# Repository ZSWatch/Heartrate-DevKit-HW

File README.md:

# ZSWatch-Heartrate-DevKit

## 📑 Table of Contents

- [ZSWatch-Heartrate-DevKit](#zswatch-heartrate-devkit)
  - [📑 Table of Contents](#-table-of-contents)
  - [📖 About](#-about)
  - [📂 Directory Breakdown](#-directory-breakdown)
  - [Purchasing](#purchasing)
  - [Ressources](#ressources)
  - [👨‍💻 Maintainer](#-maintainer)

## 📖 About

The **ZSWatch-Heartrate-DevKit** project provides the hardware design and production files for a heartrate development board tailored to the ZSWatch ecosystem.
It is built with **KiCad** and integrates a full **CI/CD pipeline** using **KiBot**, ensuring reproducible outputs for documentation, manufacturing, and releases.

Key features:

- 🛠️ Open-source hardware design
- 📦 Automated generation of Gerber, BoM, and documentation via KiBot
- 🔄 Workflow stages (DRAFT → PRELIMINARY → CHECKED → RELEASED) for structured releases
- 📝 Clear documentation and changelog to track progress
- 🌍 Designed with collaboration and transparency in mind

Please check the [wiki](https://github.com/ZSWatch/ZSWatch/wiki) for more information about the project.

You can also view this project on [CADLAB.io](https://cadlab.io/project/29659).

## 📂 Directory Breakdown

- **`.github`**: GitHub related files
- **`.gitignore`**: Ignored files list
- **`devkit`**: KiCad project for the devkit
- **`production`**: Manufacturing outputs (Gerbers, documentation, etc.)
- **`CHANGELOG.md`**: Version history
- **`LICENSE`**: Project license (GPL-3.0)
- **`README.md`**: Project overview

## Purchasing

TBD

## Ressources

- [KiBot Template](https://github.com/nguyen-v/KDT_Hierarchical_KiBot)

## 👨‍💻 Maintainer

- [Daniel Kampert](mailto:danielkameprt@kampis-elektroecke.de)

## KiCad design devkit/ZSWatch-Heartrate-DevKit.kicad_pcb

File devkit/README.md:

<h1 align="center">Template</h1>

<p align="center" width="100%">
  
</p>

***

<p align="center">
  
&nbsp; &nbsp; &nbsp; &nbsp;
  
</p>

***

## SPECIFICATIONS

| Parameter | Value |
| --- | --- |
| Dimensions | 32.0 × 24.0 mm |

***

## DIRECTORY STRUCTURE

    .
    ├─ Computations       # Misc calculations
    ├─ HTML               # HTML files for generated webpage
    ├─ Images             # Pictures and renders
    │
    ├─ kibot_resources    # External resources for KiBot
    │  ├─ colors          # Color theme for KiCad
    │  ├─ fonts           # Fonts used in the project
    │  ├─ scripts         # External scripts used with KiBot
    │  └─ templates       # Templates for KiBot generated reports
    │
    ├─ kibot_yaml         # KiBot YAML config files
    ├─ KiRI               # KiRI (PCB diff viewer) files
    │
    ├─ lib                # KiCad footprint and symbol libraries
    │  ├─ 3d_models       # Component 3D models
    │  ├─ lib_fp          # Footprint libraries
    │  └─ lib_sym         # Symbol libraries
    │
    ├─ Logos              # Logos
    │
    ├─ Manufacturing      # Assembly and fabrication documents
    │  ├─ Assembly        # Assembly documents (BoM, pos, notes)
    │  │
    │  └─ Fabrication     # Fabrication documents (ZIP, notes)
    │     ├─ Drill Tables # CSV drill tables
    │     └─ Gerbers      # Gerbers
    │
    ├─ Report             # Reports for ERC/DRC
    ├─ Schematic          # PDF of schematic
    ├─ Templates          # Title block templates
    ├─ Testing
    │  └─ Testpoints      # Testpoints tables      
    │
    └─ Variants           # Outputs for assembly variants

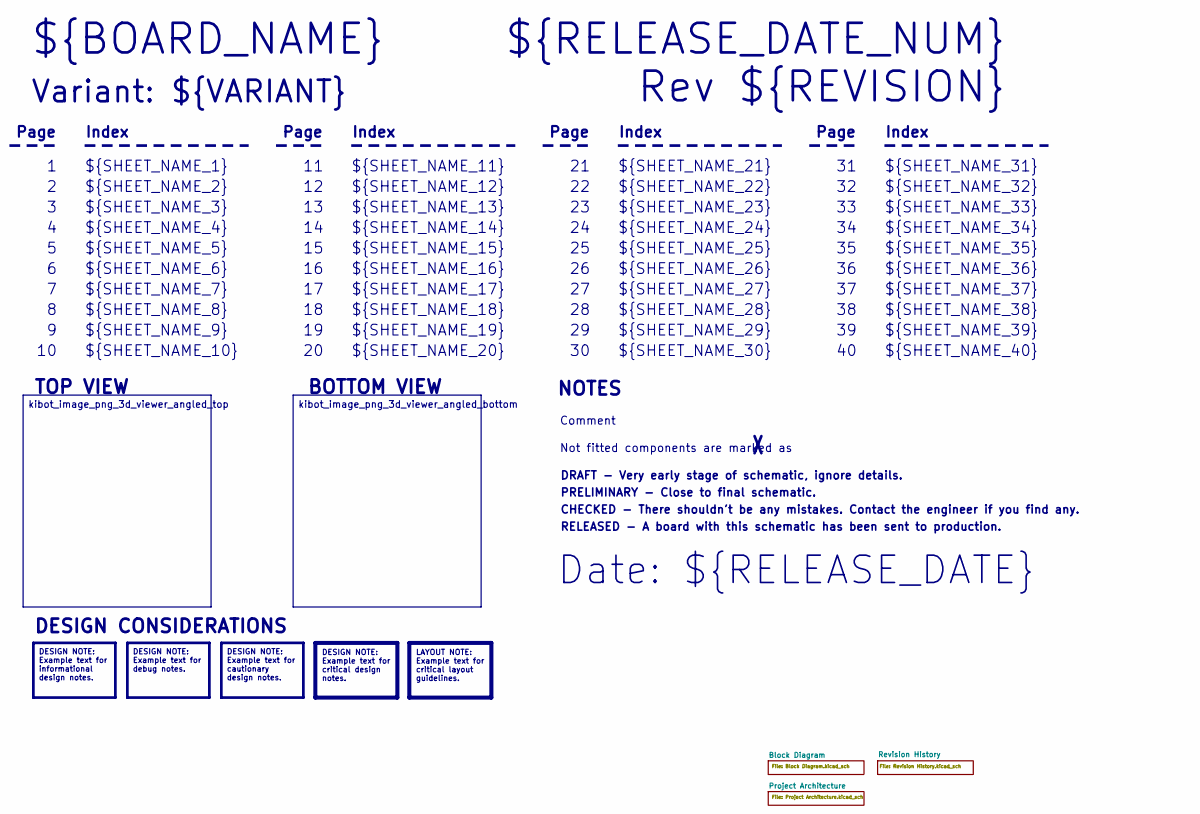
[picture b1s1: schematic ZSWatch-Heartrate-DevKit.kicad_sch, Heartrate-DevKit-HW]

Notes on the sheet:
Variant: ${VARIANT}
RELEASED - A board with this schematic has been sent to production.
${SHEET_NAME_24}
Index
Page
PRELIMINARY - Close to final schematic.
${SHEET_NAME_22}
DRAFT - Very early stage of schematic, ignore details.
${SHEET_NAME_12}
${SHEET_NAME_8}
${SHEET_NAME_2}
${SHEET_NAME_5}
${SHEET_NAME_20}
${SHEET_NAME_23}
${RELEASE_DATE_NUM}
${SHEET_NAME_35}
Not fitted components are marked as
${SHEET_NAME_11}
${SHEET_NAME_6}
${SHEET_NAME_37}
${SHEET_NAME_26}
${SHEET_NAME_36}
Rev ${REVISION}
${SHEET_NAME_15}
CHECKED - There shouldn't be any mistakes. Contact the engineer if you find any.
BOTTOM VIEW
${SHEET_NAME_14}
${SHEET_NAME_21}
${SHEET_NAME_17}
${SHEET_NAME_18}
Date: ${RELEASE_DATE}
${SHEET_NAME_7}
${SHEET_NAME_31}
${BOARD_NAME}
NOTES
${SHEET_NAME_40}
${SHEET_NAME_39}
${SHEET_NAME_32}
${SHEET_NAME_1}
${SHEET_NAME_9}

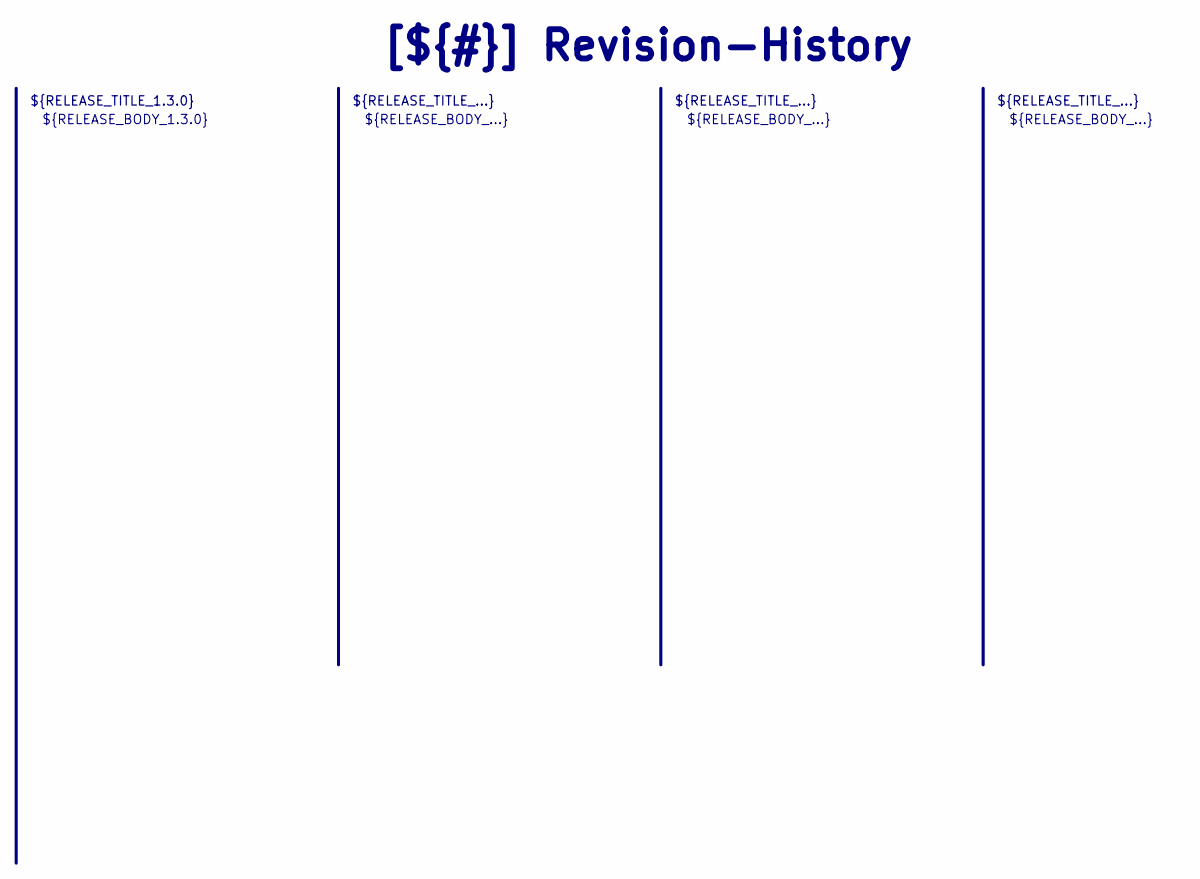
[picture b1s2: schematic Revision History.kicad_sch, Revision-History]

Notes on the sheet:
${RELEASE_BODY_...}
[${#}] ${TITLE}
${RELEASE_BODY_1.3.0}
${RELEASE_TITLE_...}
${RELEASE_TITLE_1.3.0}

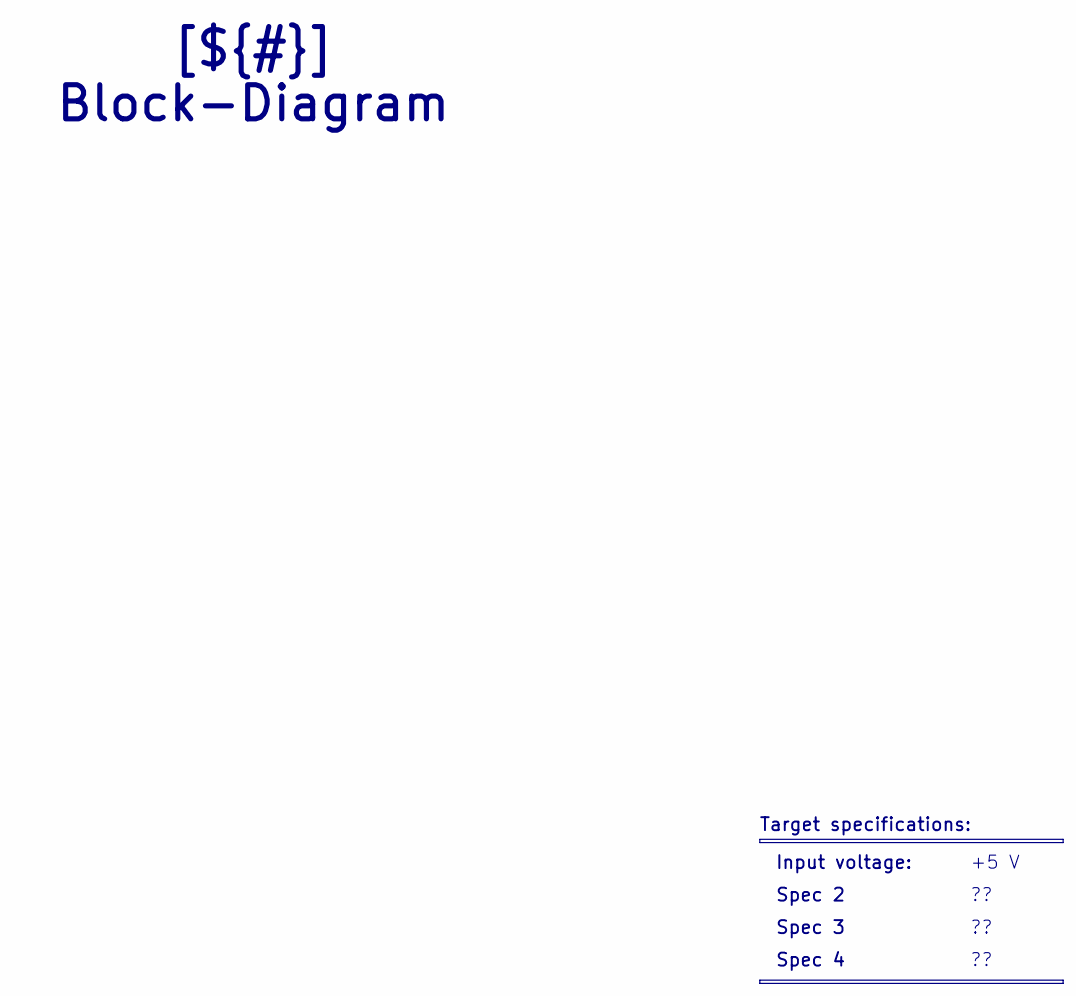
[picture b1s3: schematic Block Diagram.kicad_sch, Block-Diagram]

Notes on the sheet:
Spec 4
+5 V
[${#}] ${TITLE}
Input voltage:
Target specifications:
Spec 3
Spec 2

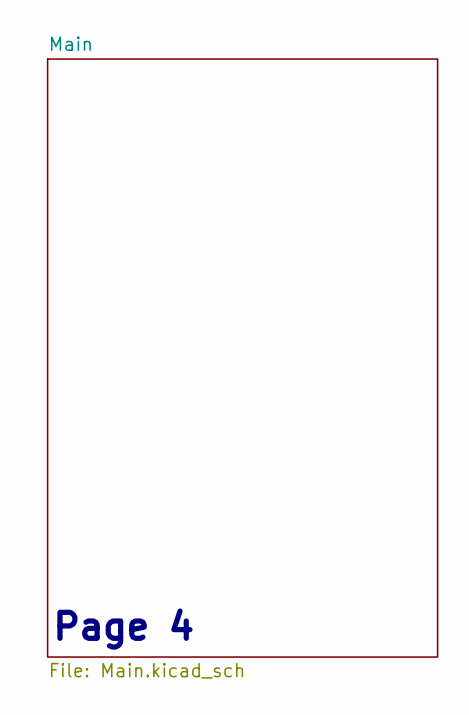
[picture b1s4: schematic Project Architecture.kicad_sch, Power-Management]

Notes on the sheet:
Page 4

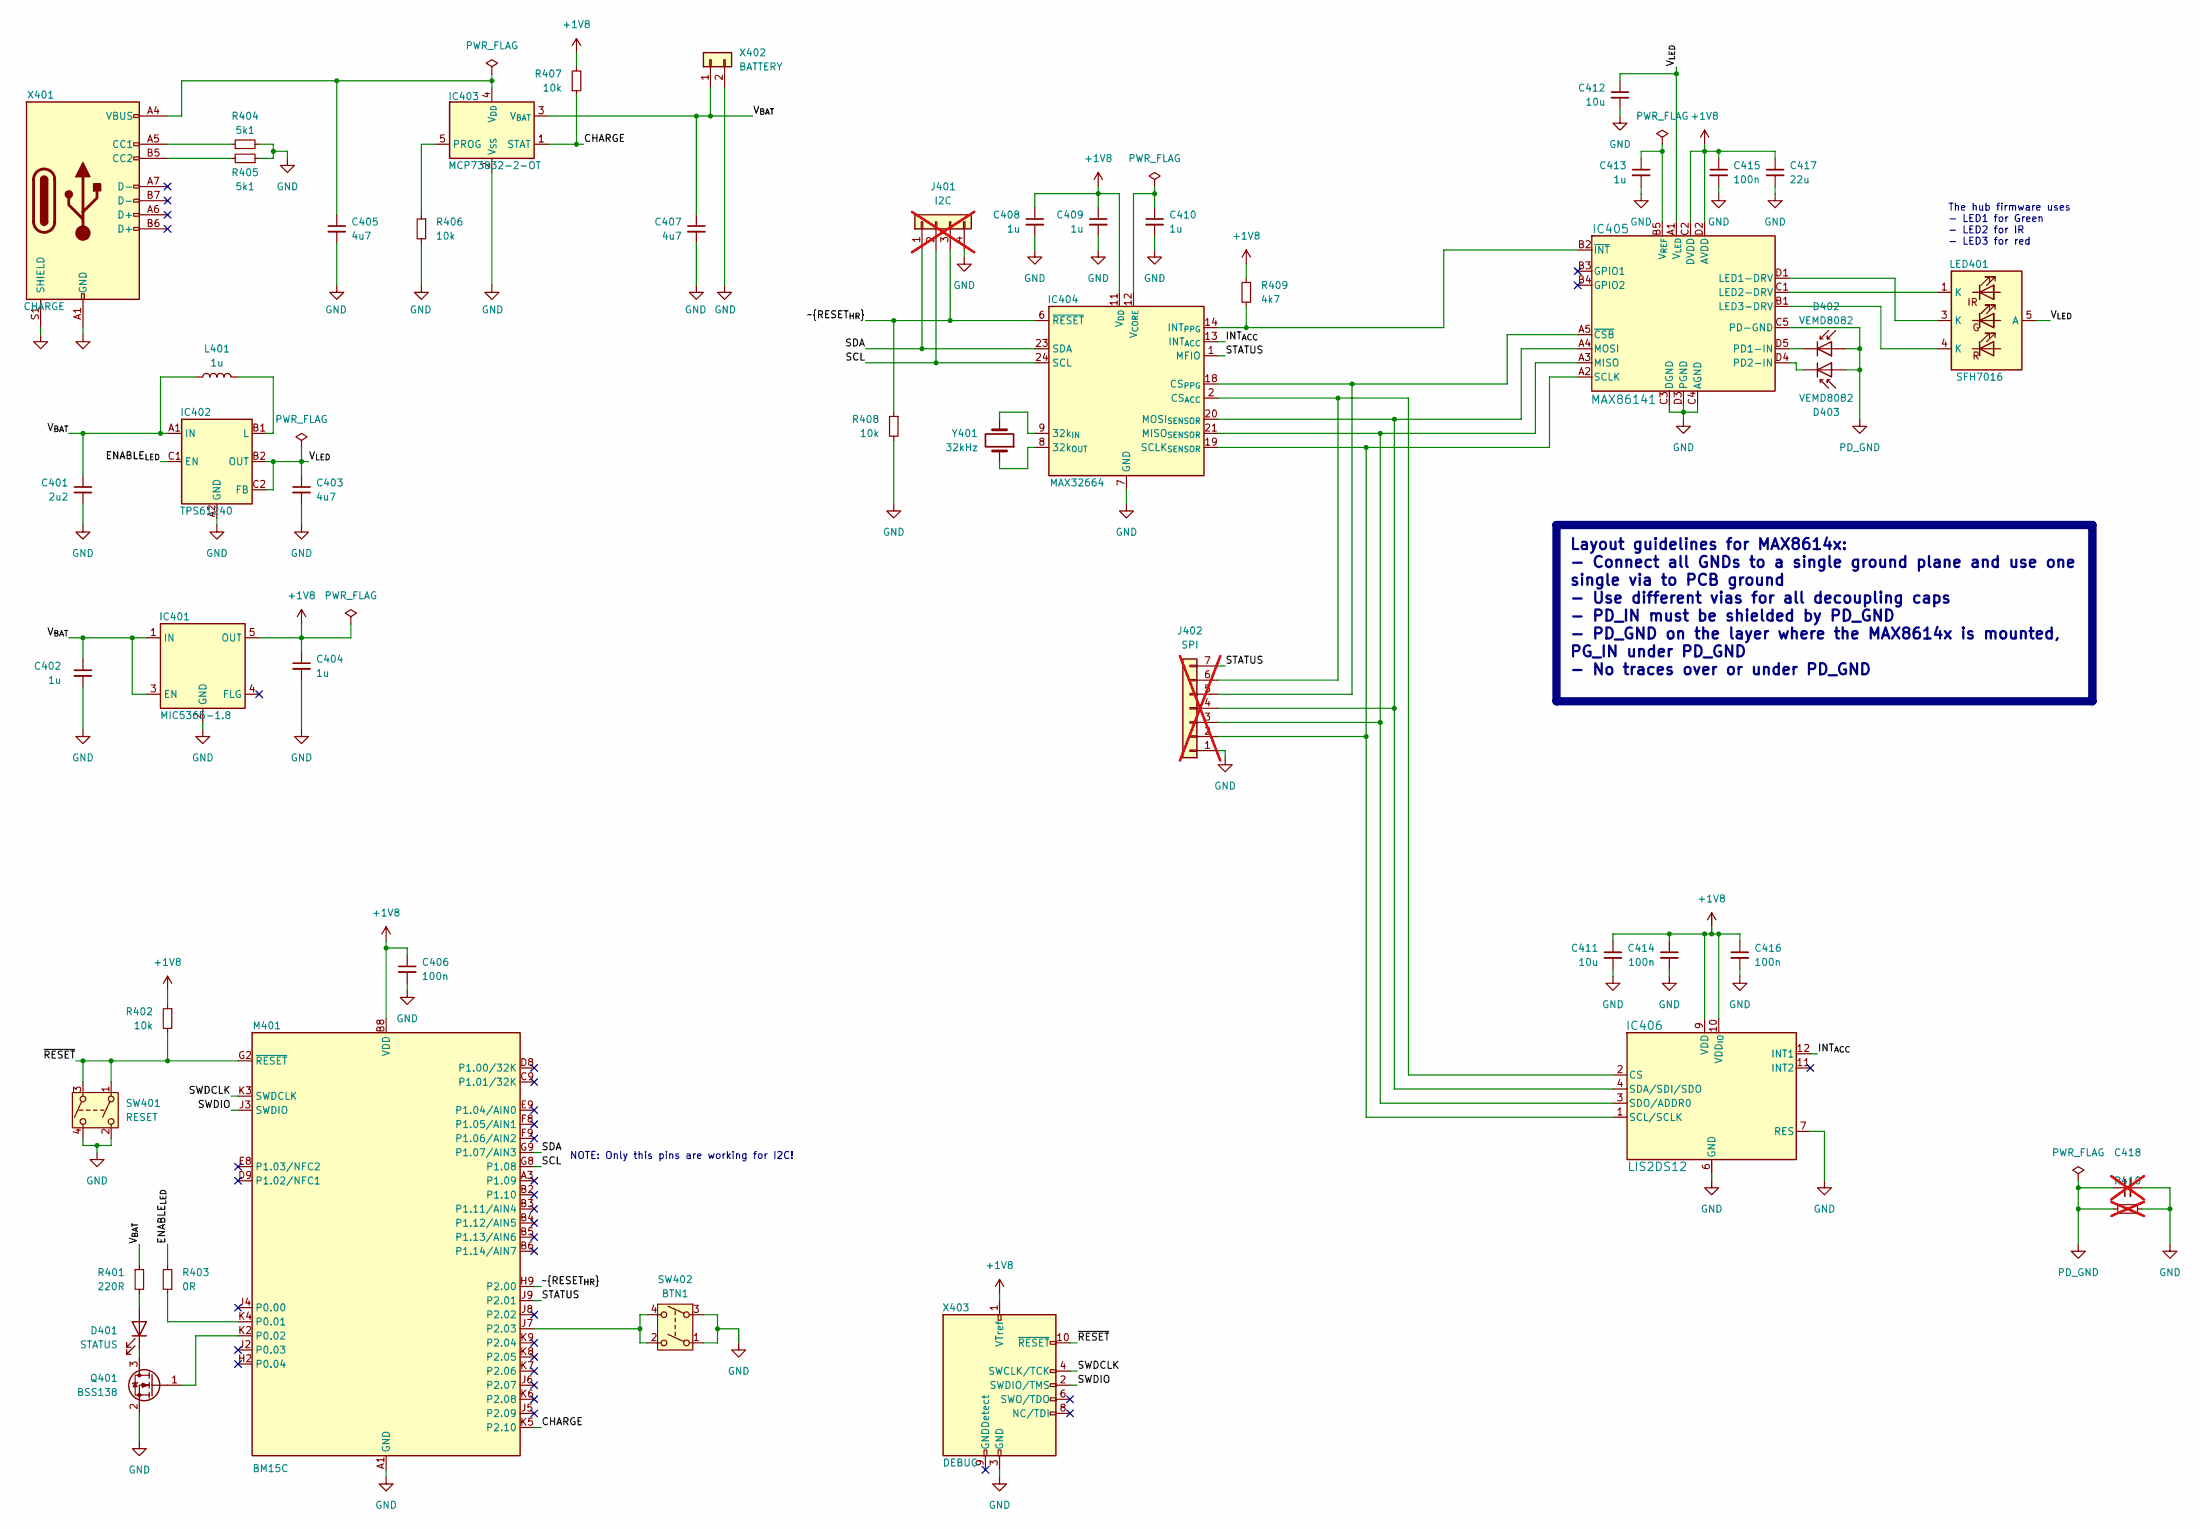
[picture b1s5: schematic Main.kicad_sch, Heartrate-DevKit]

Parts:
C401: 2u2; C_0603_1608Metric; mouser# 581-06033D225MAT2A
C402, C404: 1u; C_0603_1608Metric; mouser# 581-06035C105MAT2A
C403, C405, C407: 4u7; C_0603_1608Metric; mouser# 963-LMK107BJ475KA-T
C406, C414, C415, C416: 100n; C_0402_1005Metric; mouser# 80-C0402C104K4R7411
C408, C409, C410, C413: 1u; C_0402_1005Metric; mouser# 581-04023D105KAT2A
C411, C412: 10u; C_0402_1005Metric; mouser# 963-AMK105CBJ106MV-F
C417: 22u; C_0402_1005Metric; mouser# 963-MEASP105CC62261A
C418: C_0402_1005Metric; not fitted
D401: STATUS; LED_0805_2012Metric_Pad1.15x1.40mm_HandSolder; mouser# 630-HSMQ-C170-T0000
D402, D403: VEMD8082; VEMD808x; mouser# 78-VEMD8082
IC401: MIC5365-1.8; SOT-23-5; mouser# 998- MIC5365-1.8YD5-TR
IC402: TPS61240; DSBGA-6_0.886x1.288mm_2x3_P0.4mm; mouser# 595-TPS61240YFFR
IC403: MCP73832-2-OT; SOT-23-5; mouser# 579-MCP73832T-2ACI/OT
IC404: MAX32664; MAX32664GTG; mouser# 700-MAX32664GTGC+
IC405: MAX86141; THIN-WLP-20_2.228x1.967mm_P0.4mm; mouser# 700-MAX86141ENP+T
IC406: LIS2DS12; LGA-12_2x2mm_P0.5mm; mouser# 511-LIS2DS12
J401: I2C; PinHeader_1x04_P2.54mm_Vertical; not fitted
J402: SPI; PinHeader_1x07_P2.54mm_Vertical; not fitted
L401: 1u; L_0603_1608Metric; mouser# 815-ASMCI-0603-1R0MT
LED401: SFH7016; mouser# 720-SFH7016
M401: BM15C; mouser# 308-BM15C
Q401: BSS138; SOT-23; mouser# 512-BSS138
R401: 220R; R_0402_1005Metric; mouser# 652-CR0402-JW-221GLF
R402, R406, R407, R408: 10k; R_0402_1005Metric; mouser# 652-CR0402-JW-103GLF
R403: 0R; R_0805_2012Metric; mouser# 71-CRCW08050000Z0EBC
R404, R405: 5k1; R_0402_1005Metric; mouser# 652-CR0402-FX-5101GLF
R409: 4k7; R_0402_1005Metric; mouser# 603-RC0402FR-7D4K7L
R410: R_0402_1005Metric; not fitted
SW401: RESET; WS-TASV-6x6; mouser# 710-430182095816
SW402: BTN1; WS-TASV-6x6; mouser# 710-430182095816
X401: CHARGE; USB_C_Receptacle_GCT_USB4105-xx-A_16P_TopMnt_Horizontal; mouser# 640-USB4105-GF-A-120
X402: BATTERY; 78171-0002; mouser# 538-78171-0002
X403: DEBUG; PinHeader_2x05_P1.27mm_Vertical; mouser# 710-62201021121
Y401: 32kHz; ECS_ECX-1210; mouser# 520-.327-6-1210-TR

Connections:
+1V8: C404.1, C406.1, C408.1, C409.1, C411.1, C414.1, C415.1, C416.1, C417.1, IC401.5 (OUT), IC404.11 (V_{DD}), IC404.22 (V_{DD}), IC405.C2 (DVDD), IC405.D2 (AVDD), IC406.9 (VDD), IC406.10 (VDD_{IO}), M401.B8 (VDD), M401.C8 (VDD), R402.1, R407.2, R409.1, X403.1 (VTref)
/Project Architecture/Main/CHARGE: IC403.1 (STAT), M401.K5 (P2.10), R407.1
/Project Architecture/Main/ENABLE_{LED}: IC402.C1 (EN), R403.2
/Project Architecture/Main/INT_{ACC}: IC404.13 (INT_{ACC}), IC406.12 (INT1)
/Project Architecture/Main/SCL: IC404.24 (SCL), J401.2, M401.G8 (P1.08)
/Project Architecture/Main/SDA: IC404.23 (SDA), J401.1, M401.G9 (P1.07/AIN3)
/Project Architecture/Main/STATUS: IC404.1 (MFIO), J402.7, M401.J9 (P2.01)
/Project Architecture/Main/SWDCLK: M401.K3 (SWDCLK), X403.4 (SWCLK/TCK)
/Project Architecture/Main/SWDIO: M401.J3 (SWDIO), X403.2 (SWDIO/TMS)
/Project Architecture/Main/V_{BAT}: C401.1, C402.1, C407.1, IC401.1 (IN), IC401.3 (EN), IC402.A1 (IN), IC403.3 (V_{BAT}), L401.1, R401.1, X402.1
/Project Architecture/Main/V_{LED}: C403.1, C412.1, IC402.B2 (OUT), IC402.C2 (FB), IC405.A1 (V_{LED}), LED401.2 (A), LED401.5 (A)
/Project Architecture/Main/~RESET_{HR}: IC404.6 (~RESET), J401.3, M401.H9 (P2.00), R408.1
/Project Architecture/Main/~RESET: M401.G2 (~RESET), R402.2, SW401.1, SW401.3, X403.10 (~RESET)
GND: C401.2, C402.2, C403.2, C404.2, C405.2, C406.2, C407.2, C408.2, C409.2, C410.2, C411.2, C412.2, C413.2, C414.2, C415.2, C416.2, C417.2, C418.2, IC401.2 (GND), IC402.A2 (GND), IC403.2 (V_{SS}), IC404.7 (GND), IC404.10 (GND), IC405.C3 (DGND), IC405.C4 (AGND), IC405.D3 (PGND), IC406.6 (GND), IC406.7 (RES), IC406.8 (GND), J401.4, J402.1, M401.A1 (GND), M401.A9 (GND), M401.B1 (GND), M401.B7 (GND), M401.B9 (GND), M401.D1 (GND), M401.E1 (GND), M401.F1 (GND), M401.H8 (GND), Q401.2 (S), R404.2, R405.1, R406.2, R408.2, R410.2, SW401.2, SW401.4, SW402.1, SW402.3, X401.A1 (GND), X401.A12 (GND), X401.B1 (GND), X401.B12 (GND), X401.S1 (SHIELD), X402.2, X403.3 (GND), X403.5 (GND)
unnamed: D401.2 (A), R401.2
unnamed: D401.1 (K), Q401.3 (D)
unnamed: D402.1 (K), IC405.D5 (PD1-IN)
unnamed: D403.1 (K), IC405.D4 (PD2-IN)
unnamed: IC402.B1 (L), L401.2
unnamed: IC403.5 (PROG), R406.1
unnamed: C405.1, IC403.4 (V_{DD}), X401.A4 (VBUS), X401.A9 (VBUS), X401.B4 (VBUS), X401.B9 (VBUS)
unnamed: IC404.9 (32k_{IN}), Y401.2
unnamed: IC404.8 (32k_{OUT}), Y401.1
unnamed: IC404.2 (CS_{ACC}), IC406.2 (CS), J402.6
unnamed: IC404.18 (CS_{PPG}), IC405.A5 (~CSB), J402.5
unnamed: IC404.14 (INT_{PPG}), IC405.B2 (~INT), R409.2
unnamed: IC404.21 (MISO_{SENSOR}), IC405.A3 (MISO), IC406.3 (SDO/ADDR0), J402.3
unnamed: IC404.20 (MOSI_{SENSOR}), IC405.A4 (MOSI), IC406.4 (SDA/SDI/SDO), J402.4
unnamed: IC404.19 (SCLK_{SENSOR}), IC405.A2 (SCLK), IC406.1 (SCL/SCLK), J402.2
unnamed: C410.1, IC404.12 (V_{CORE})
unnamed: IC405.D1 (LED1-DRV), LED401.3 (K)
unnamed: IC405.C1 (LED2-DRV), LED401.1 (K)
unnamed: IC405.B1 (LED3-DRV), LED401.4 (K)
unnamed: C413.1, IC405.B5 (V_{REF})
unnamed: M401.K4 (P0.01), R403.1
unnamed: M401.K2 (P0.02), Q401.1 (G)
unnamed: M401.J7 (P2.03), SW402.2, SW402.4
unnamed: R404.1, X401.A5 (CC1)
unnamed: R405.2, X401.B5 (CC2)
PD_GND: C418.1, D402.2 (A), D403.2 (A), IC405.C5 (PD-GND), R410.1

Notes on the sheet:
The hub firmware uses - LED1 for Green - LED2 for IR - LED3 for red
NOTE: Only this pins are working for I2C!
Layout guidelines for MAX8614x: - Connect all GNDs to a single ground plane and use one single via to PCB ground - Use different vias for all decoupling caps - PD_IN must be shielded by PD_GND - PD_GND on the layer where the MAX8614x is mounted, PG_IN under PD_GND - No traces over or under PD_GND

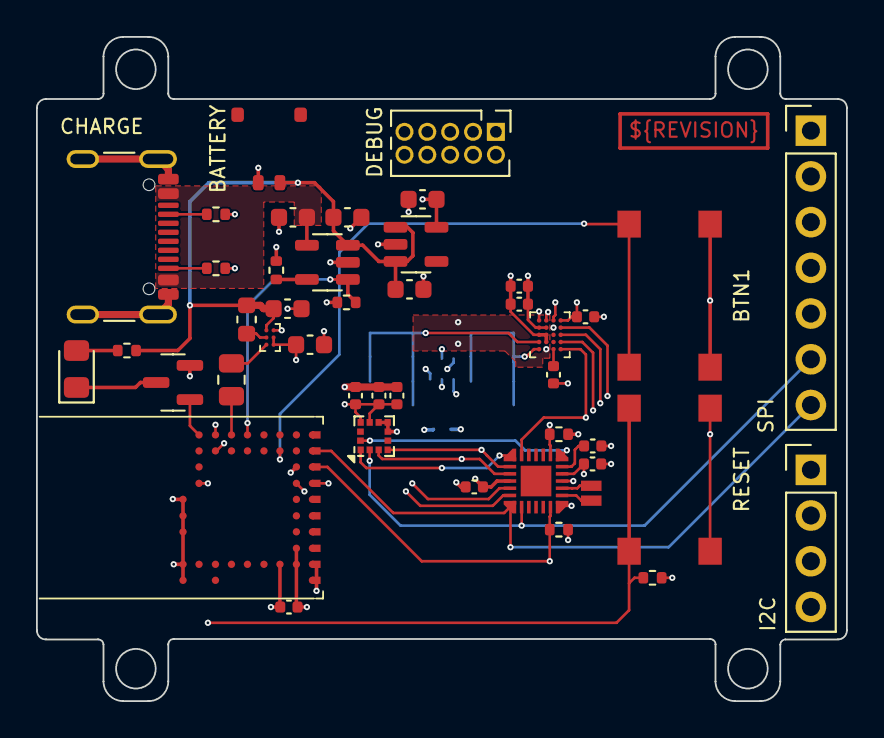
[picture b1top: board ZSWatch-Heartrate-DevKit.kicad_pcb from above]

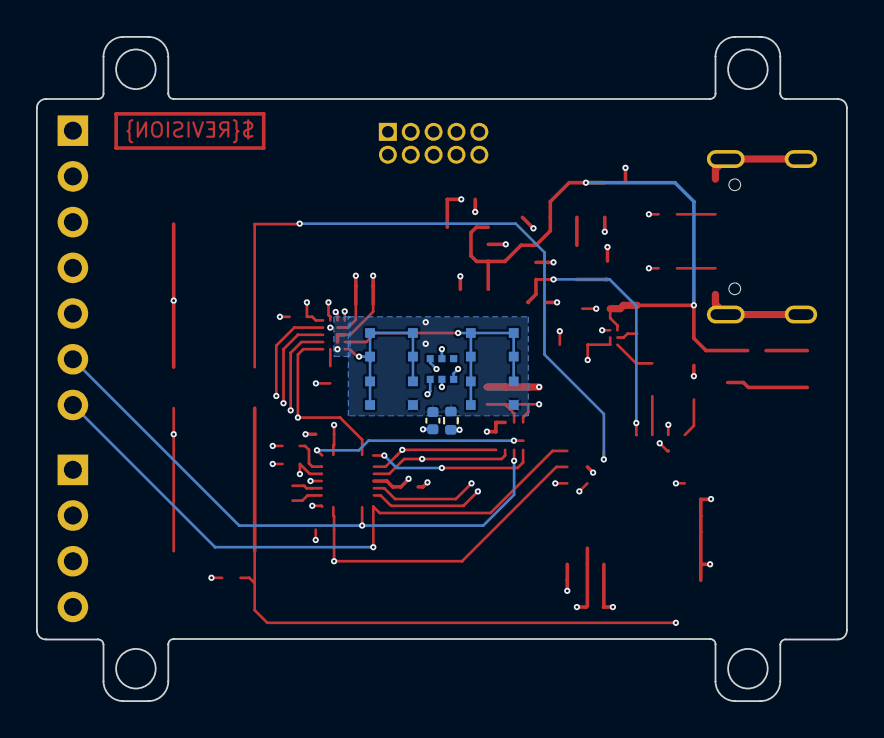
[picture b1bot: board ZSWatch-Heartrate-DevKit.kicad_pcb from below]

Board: 4 copper layers, 45.0 x 36.9 mm, 49 parts (5 on the bottom side), 40 nets.

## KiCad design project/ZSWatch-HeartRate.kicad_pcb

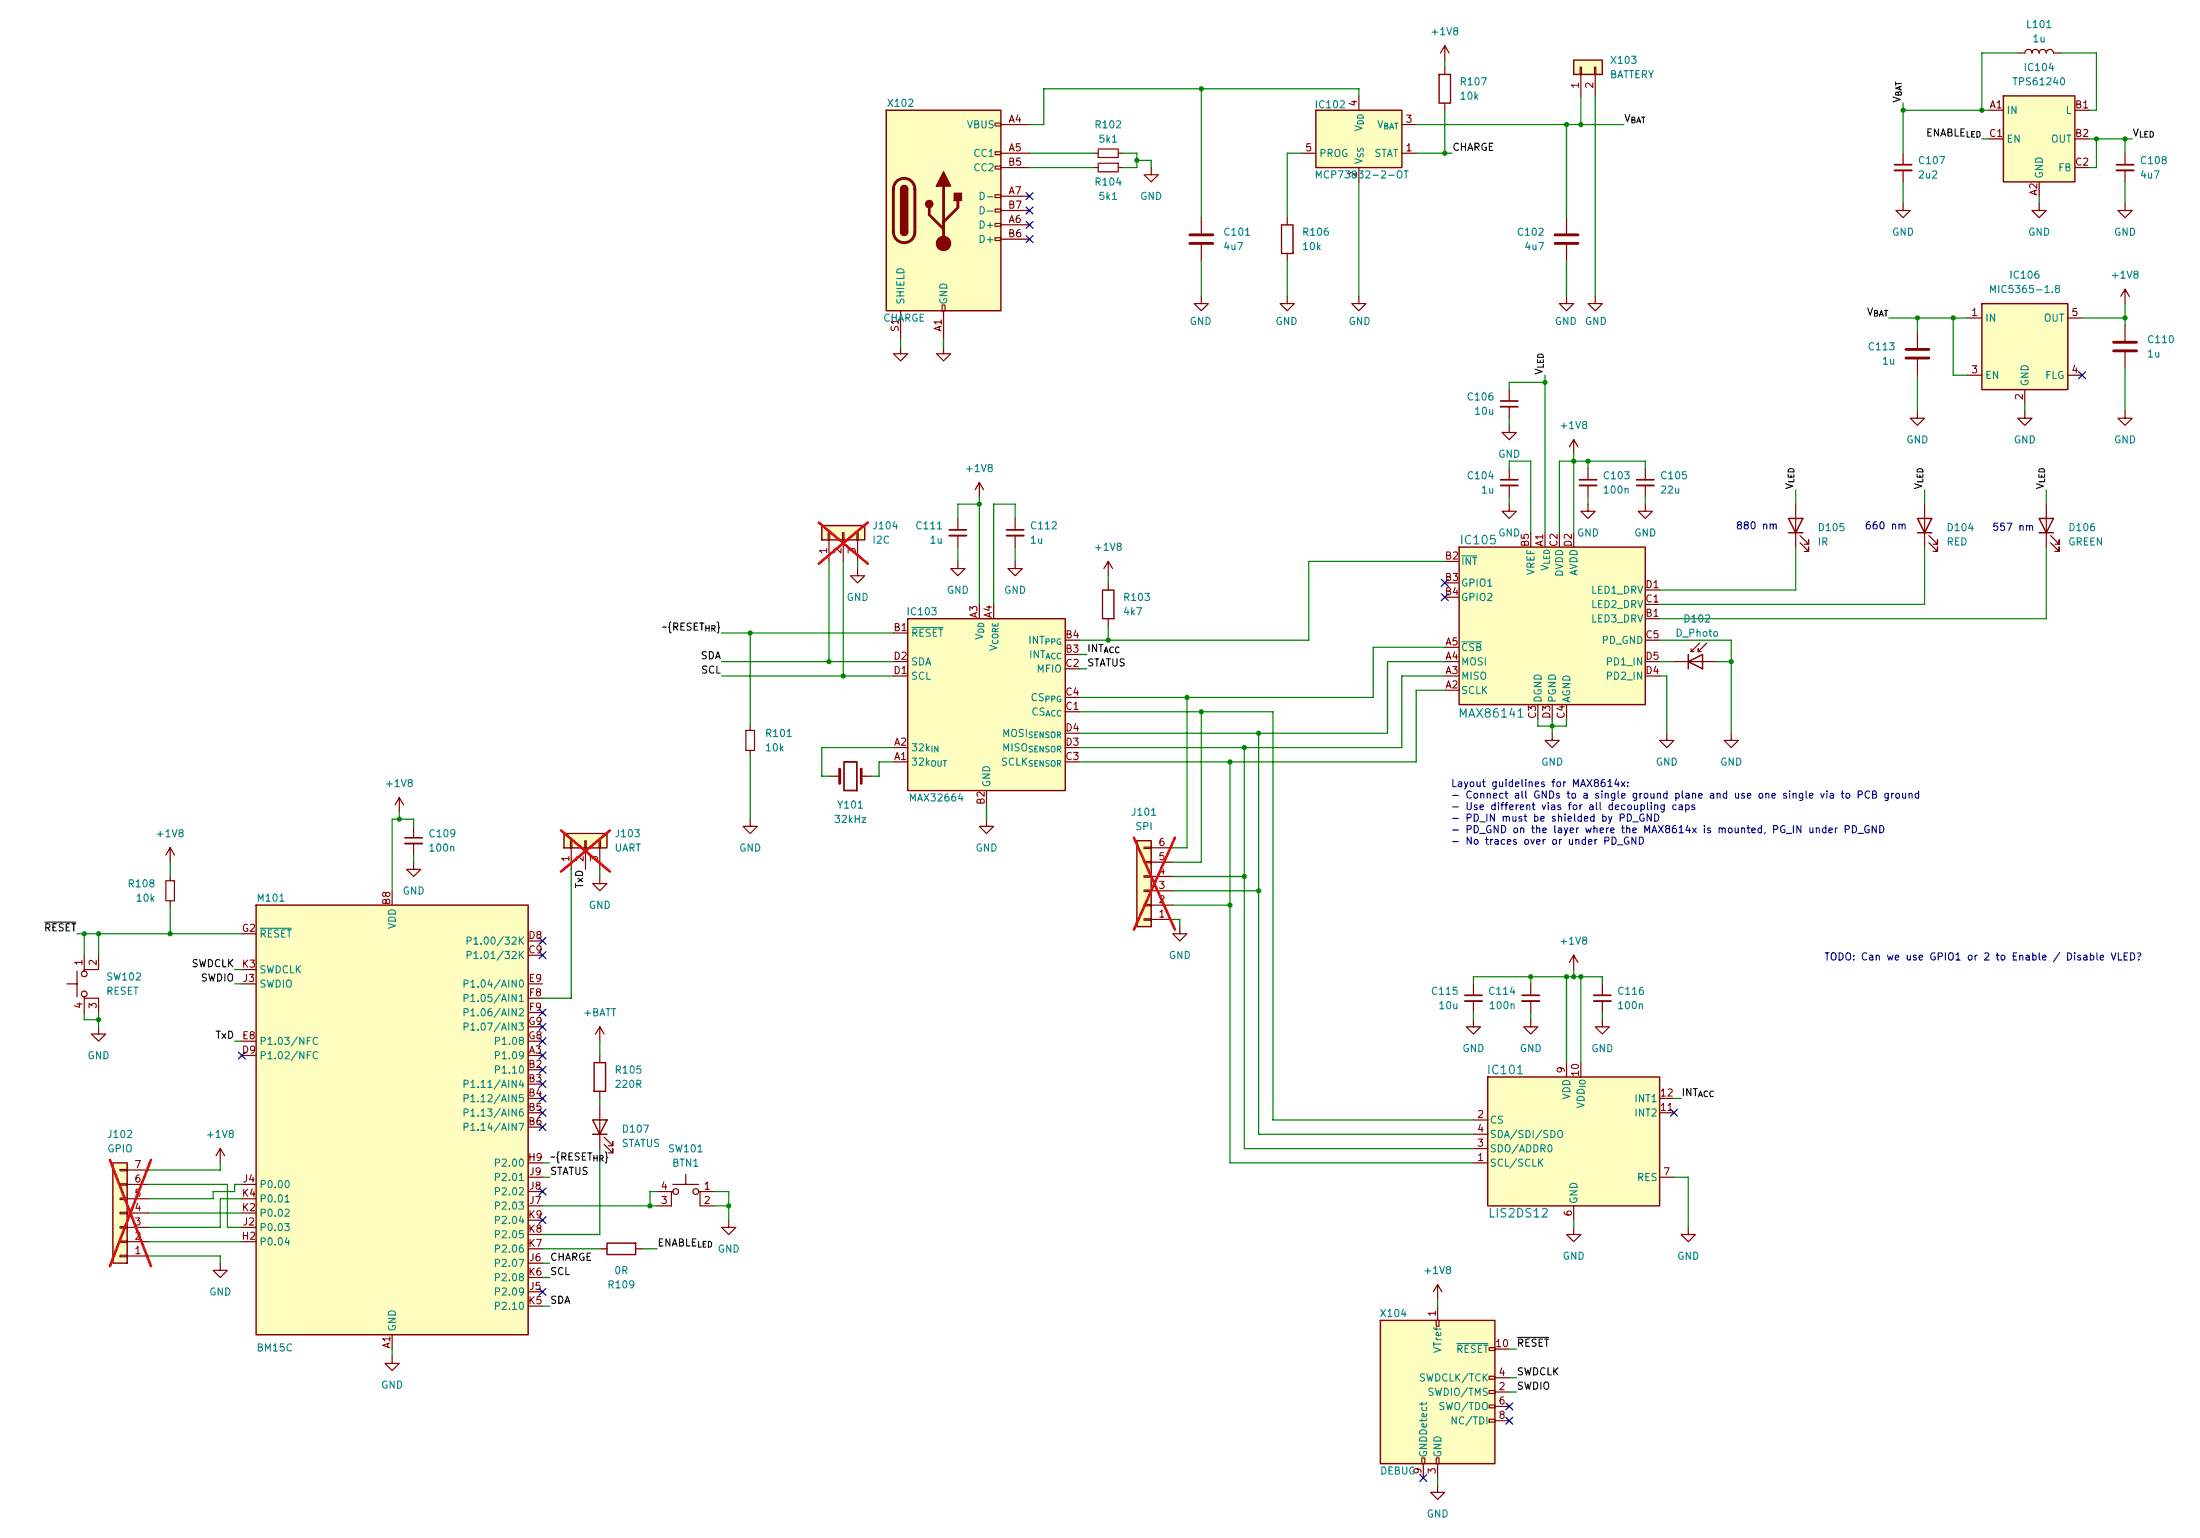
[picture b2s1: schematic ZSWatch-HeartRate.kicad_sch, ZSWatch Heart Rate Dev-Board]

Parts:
C101, C102, C108: 4u7; C_0603_1608Metric
C103, C114, C116: 100n; C_0402_1005Metric
C104, C111, C112: 1u; C_0402_1005Metric
C105: 22u; C_0402_1005Metric
C106, C115: 10u; C_0402_1005Metric
C107: 2u2; C_0603_1608Metric
C109: 100n; C_0603_1608Metric
C110, C113: 1u; C_0603_1608Metric; mouser# 581-06035C105MAT2A
D102: D_Photo; VEMD5080X01; mouser# 78-VEMD5080X01
D104: RED; D_0603_1608Metric; mouser# 606-7017X1
D105: IR; D_0603_1608Metric; mouser# 604-APTD1608SF4C
D106: GREEN; D_0603_1608Metric; mouser# 749-SM0603PGC
D107: STATUS; LED_0805_2012Metric_Pad1.15x1.40mm_HandSolder; mouser# 630-HSMQ-C170-T0000
IC101: LIS2DS12; LGA-12_2x2mm_P0.5mm
IC102: MCP73832-2-OT; SOT-23-5; mouser# 579-MCP73832T-2ACI/OT
IC103: MAX32664; WLP-16_2x2mm_P0.5mm
IC104: TPS61240; DSBGA-6_0.886x1.288mm_2x3_P0.4mm; mouser# 595-TPS61240YFFR
IC105: MAX86141; THIN-WLP-20_2.228x1.967mm_P0.4mm; mouser# 700-MAX86141ENP+T
IC106: MIC5365-1.8; SOT-23-5; mouser# 998-MIC5365-1.8YC5-TR
J101: SPI; PinHeader_1x06_P2.54mm_Vertical; not fitted
J102: GPIO; PinHeader_1x07_P2.54mm_Vertical; not fitted
J103: UART; PinHeader_1x03_P2.54mm_Vertical; not fitted
J104: I2C; PinHeader_1x03_P2.54mm_Vertical; not fitted
L101: 1u; L_0603_1608Metric
M101: BM15C; mouser# 308-BM15C
R101, R106, R107, R108: 10k; C_0603_1608Metric
R102, R104: 5k1; R_0603_1608Metric
R103: 4k7; R_0402_1005Metric
R105: 220R; C_0603_1608Metric; mouser# 652-CR0402-JW-221GLF
R109: 0R; R_0805_2012Metric
SW101: BTN1; WS-TASV-6x6; mouser# 710-430182095816
SW102: RESET; WS-TASV-6x6; mouser# 710-430182095816
X102: CHARGE; USB_C_Receptacle_GCT_USB4105-xx-A_16P_TopMnt_Horizontal
X103: BATTERY; 78171-0002
X104: DEBUG; PinHeader_2x05_P1.27mm_Vertical; mouser# 200-SHF-105-01-L-D-TH-TR
Y101: 32kHz; ECS_ECX-1210

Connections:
+1V8: C103.1, C105.1, C109.1, C110.1, C111.1, C114.1, C115.1, C116.1, IC101.9 (VDD), IC101.10 (VDD_{IO}), IC103.A3 (V_{DD}), IC105.C2 (DVDD), IC105.D2 (AVDD), IC106.5 (OUT), J102.7, M101.B8 (VDD), M101.C8 (VDD), R103.1, R107.2, R108.1, X104.1 (VTref)
+BATT: R105.1
/CHARGE: IC102.1 (STAT), M101.J6 (P2.07), R107.1
/ENABLE_{LED}: IC104.C1 (EN), R109.2
/INT_{ACC}: IC101.12 (INT1), IC103.B3 (INT_{ACC})
/SCL: IC103.D1 (SCL), J104.2, M101.K6 (P2.08)
/SDA: IC103.D2 (SDA), J104.1, M101.K5 (P2.10)
/STATUS: IC103.C2 (MFIO), M101.J9 (P2.01)
/SWDCLK: M101.K3 (SWDCLK), X104.4 (SWDCLK/TCK)
/SWDIO: M101.J3 (SWDIO), X104.2 (SWDIO/TMS)
/TxD: J103.2, M101.E8 (P1.03/NFC)
/V_{BAT}: C102.1, C107.1, C113.1, IC102.3 (V_{BAT}), IC104.A1 (IN), IC106.1 (IN), IC106.3 (EN), L101.1, X103.1
/V_{LED}: C106.1, C108.1, D104.2 (A), D105.2 (A), D106.2 (A), IC104.B2 (OUT), IC104.C2 (FB), IC105.A1 (V_{LED})
/~RESET_{HR}: IC103.B1 (~RESET), M101.H9 (P2.00), R101.1
/~RESET: M101.G2 (~RESET), R108.2, SW102.1, SW102.2, X104.10 (~RESET)
GND: C101.2, C102.2, C103.2, C104.2, C105.2, C106.2, C107.2, C108.2, C109.2, C110.2, C111.2, C112.2, C113.2, C114.2, C115.2, C116.2, D102.2 (A), IC101.6 (GND), IC101.7 (RES), IC101.8 (GND), IC102.2 (V_{SS}), IC103.B2 (GND), IC104.A2 (GND), IC105.C3 (DGND), IC105.C4 (AGND), IC105.C5 (PD_GND), IC105.D3 (PGND), IC105.D4 (PD2_IN), IC106.2 (GND), J101.1, J102.1, J103.3, J104.3, M101.A1 (GND), M101.A9 (GND), M101.B1 (GND), M101.B7 (GND), M101.B9 (GND), M101.D1 (GND), M101.E1 (GND), M101.F1 (GND), M101.H8 (GND), R101.2, R102.2, R104.1, R106.2, SW101.1, SW101.2, SW102.3 (K), SW102.4 (A), X102.A1 (GND), X102.A12 (GND), X102.B1 (GND), X102.B12 (GND), X102.S1 (SHIELD), X103.2, X104.3 (GND), X104.5 (GND)
unnamed: D102.1 (K), IC105.D5 (PD1_IN)
unnamed: D104.1 (K), IC105.C1 (LED2_DRV)
unnamed: D105.1 (K), IC105.D1 (LED1_DRV)
unnamed: D106.1 (K), IC105.B1 (LED3_DRV)
unnamed: D107.2 (A), R105.2
unnamed: D107.1 (K), M101.K8 (P2.05)
unnamed: IC101.2 (CS), IC103.C1 (CS_{ACC}), J101.5
unnamed: IC101.1 (SCL/SCLK), IC103.C3 (SCLK_{SENSOR}), IC105.A2 (SCLK), J101.2
unnamed: IC101.4 (SDA/SDI/SDO), IC103.D4 (MOSI_{SENSOR}), IC105.A4 (MOSI), J101.3
unnamed: IC101.3 (SDO/ADDR0), IC103.D3 (MISO_{SENSOR}), IC105.A3 (MISO), J101.4
unnamed: IC102.5 (PROG), R106.1
unnamed: C101.1, IC102.4 (V_{DD}), X102.A4 (VBUS), X102.A9 (VBUS), X102.B4 (VBUS), X102.B9 (VBUS)
unnamed: IC103.A2 (32k_{IN}), Y101.2
unnamed: IC103.A1 (32k_{OUT}), Y101.1
unnamed: IC103.C4 (CS_{PPG}), IC105.A5 (~CSB), J101.6
unnamed: IC103.B4 (INT_{PPG}), IC105.B2 (~INT), R103.2
unnamed: C112.1, IC103.A4 (V_{CORE})
unnamed: IC104.B1 (L), L101.2
unnamed: C104.1, IC105.B5 (VREF)
unnamed: J102.2, M101.H2 (P0.04)
unnamed: J102.3, M101.K4 (P0.01)
unnamed: J102.4, M101.K2 (P0.02)
unnamed: J102.5, M101.J4 (P0.00)
unnamed: J102.6, M101.J2 (P0.03)
unnamed: J103.1, M101.F8 (P1.05/AIN1)
unnamed: M101.J7 (P2.03), SW101.3 (K), SW101.4 (A)
unnamed: M101.K7 (P2.06), R109.1
unnamed: R102.1, X102.A5 (CC1)
unnamed: R104.2, X102.B5 (CC2)

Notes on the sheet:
557 nm
TODO: Can we use GPIO1 or 2 to Enable / Disable VLED?
Layout guidelines for MAX8614x: - Connect all GNDs to a single ground plane and use one single via to PCB ground - Use different vias for all decoupling caps - PD_IN must be shielded by PD_GND - PD_GND on the layer where the MAX8614x is mounted, PG_IN under PD_GND - No traces over or under PD_GND
660 nm
880 nm

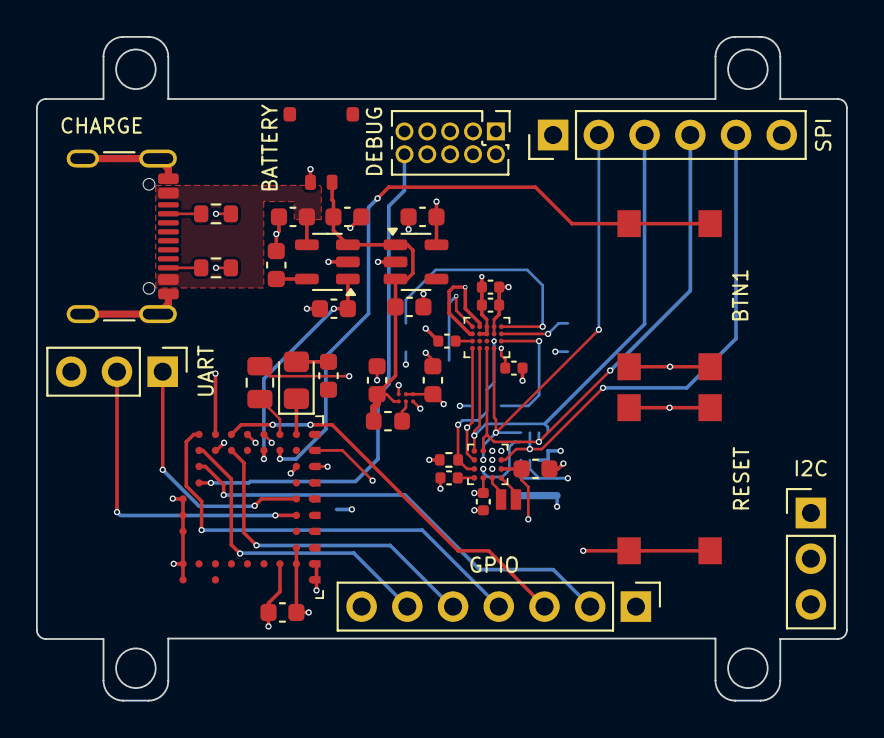
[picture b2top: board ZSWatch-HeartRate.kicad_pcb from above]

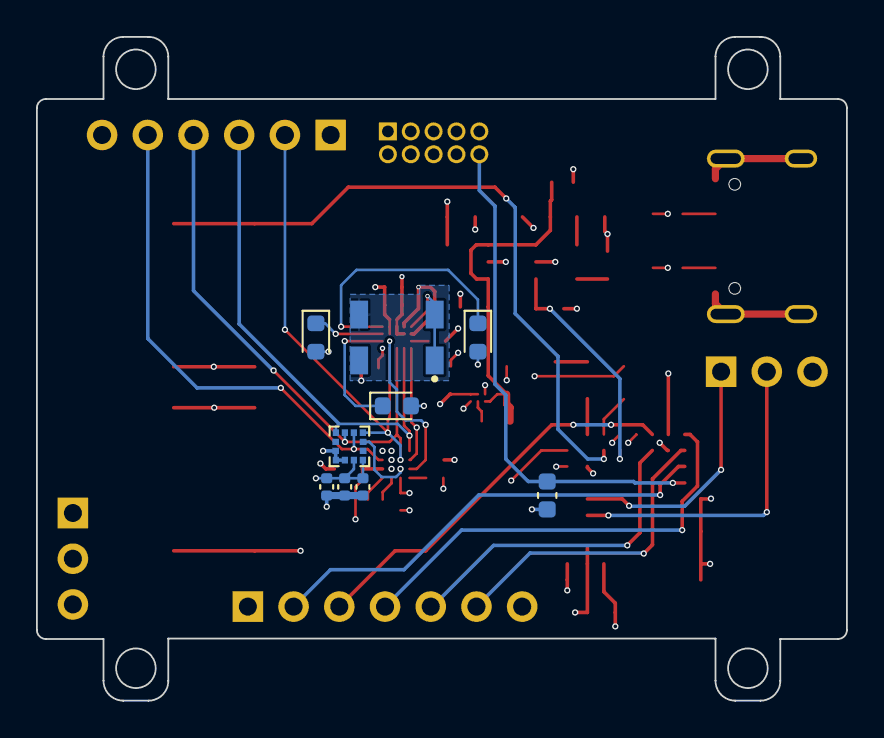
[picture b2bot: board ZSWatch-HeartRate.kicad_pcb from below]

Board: 4 copper layers, 45.0 x 36.9 mm, 48 parts (9 on the bottom side), 44 nets.

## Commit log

2024-03-03 Initialize branch with version 0.0.1
2024-03-03 Fix CI/CD errors
2024-04-12 - Working on version 1
2025-03-28 First dev board version
2025-04-18 Update CI/CD pipeline
2025-04-22 Fix wrong MAX32664 footprint
2025-05-20 Start with rev 3, fix distance between programming and battery connector, fix wrong I2C pins
2025-05-20 Add image from CI/CD action
2025-07-29 Add GitHub URL, switch to KiCad 9
2025-07-29 Update documentation and CI/CD pipeline
2025-07-29 Issue #2
2025-07-29 Add missing part informations
2025-08-01 Issue #4
2025-08-07 Rework heartrate sensor
    - Issue #7
    - Issue #6
    - Issue #5
    - Issue #4
2025-08-18 Issue #8
2025-08-18 Final check from Daniel before production
2025-08-24 Add MFIO to SPI header
2025-08-29 Fix CI/CD
2025-08-29 Update changelog
2025-09-04 Feature: Issue #4
    - Add a second photo diode to improve the measurements
2025-09-04 doc: Add missing part informations
2025-09-04 Feature: Issue #16
    - Add MFIO to SPI header
2025-09-04 Feature: Issue #8
    - Replace VEMD8080 with VEMD8082
2025-09-04 Feature: Issue #7, Issue #5
    - Replace the single R, G and IR LED with a tri color LED
    - Fix wrong I2C pins for nRF54L15
2025-09-04 Bug: Issue #14
    - Fix distance between programming and battery connector
2025-09-04 Task: Issue #15
    - Switch to KiCad 9
2025-09-04 doc: Update documentation and CI/CD pipeline
2025-09-04 Bug: Issue #2
    - Fix wrong circuit for the status LED
2025-09-04 doc: Switch to new KiCad template
2025-09-04 Task: Issue #11
    - Add block diagram to documentation
2025-09-04 Prepare release
    - Set variant to CHECKED
    - Remove unused files
    - Fix ERC errors
    - Fix DRC errors
    - Fix different documentation errors
    - Fix different path errors for the release build
2025-09-04 doc: Update documentation
    - Update README
    - Update ref designators
    - Update CI/CD pipeline
2025-09-06 Update outputs (release)
2025-10-08 Backlink to CADLAB.io has been added.
2025-11-07 Initialize development branch for version 1.3.1
2025-11-07 Bug: Issue #19
    - Remove logs from pipeline results
    Closes: #19
2025-11-07 Bug: Issue #17
    - Wrong part number for SWD connector
    Closes: #17
2025-11-07 Feature: Issue #20
    - Add commit template
    Closes: #20
2025-11-15 Align titles
